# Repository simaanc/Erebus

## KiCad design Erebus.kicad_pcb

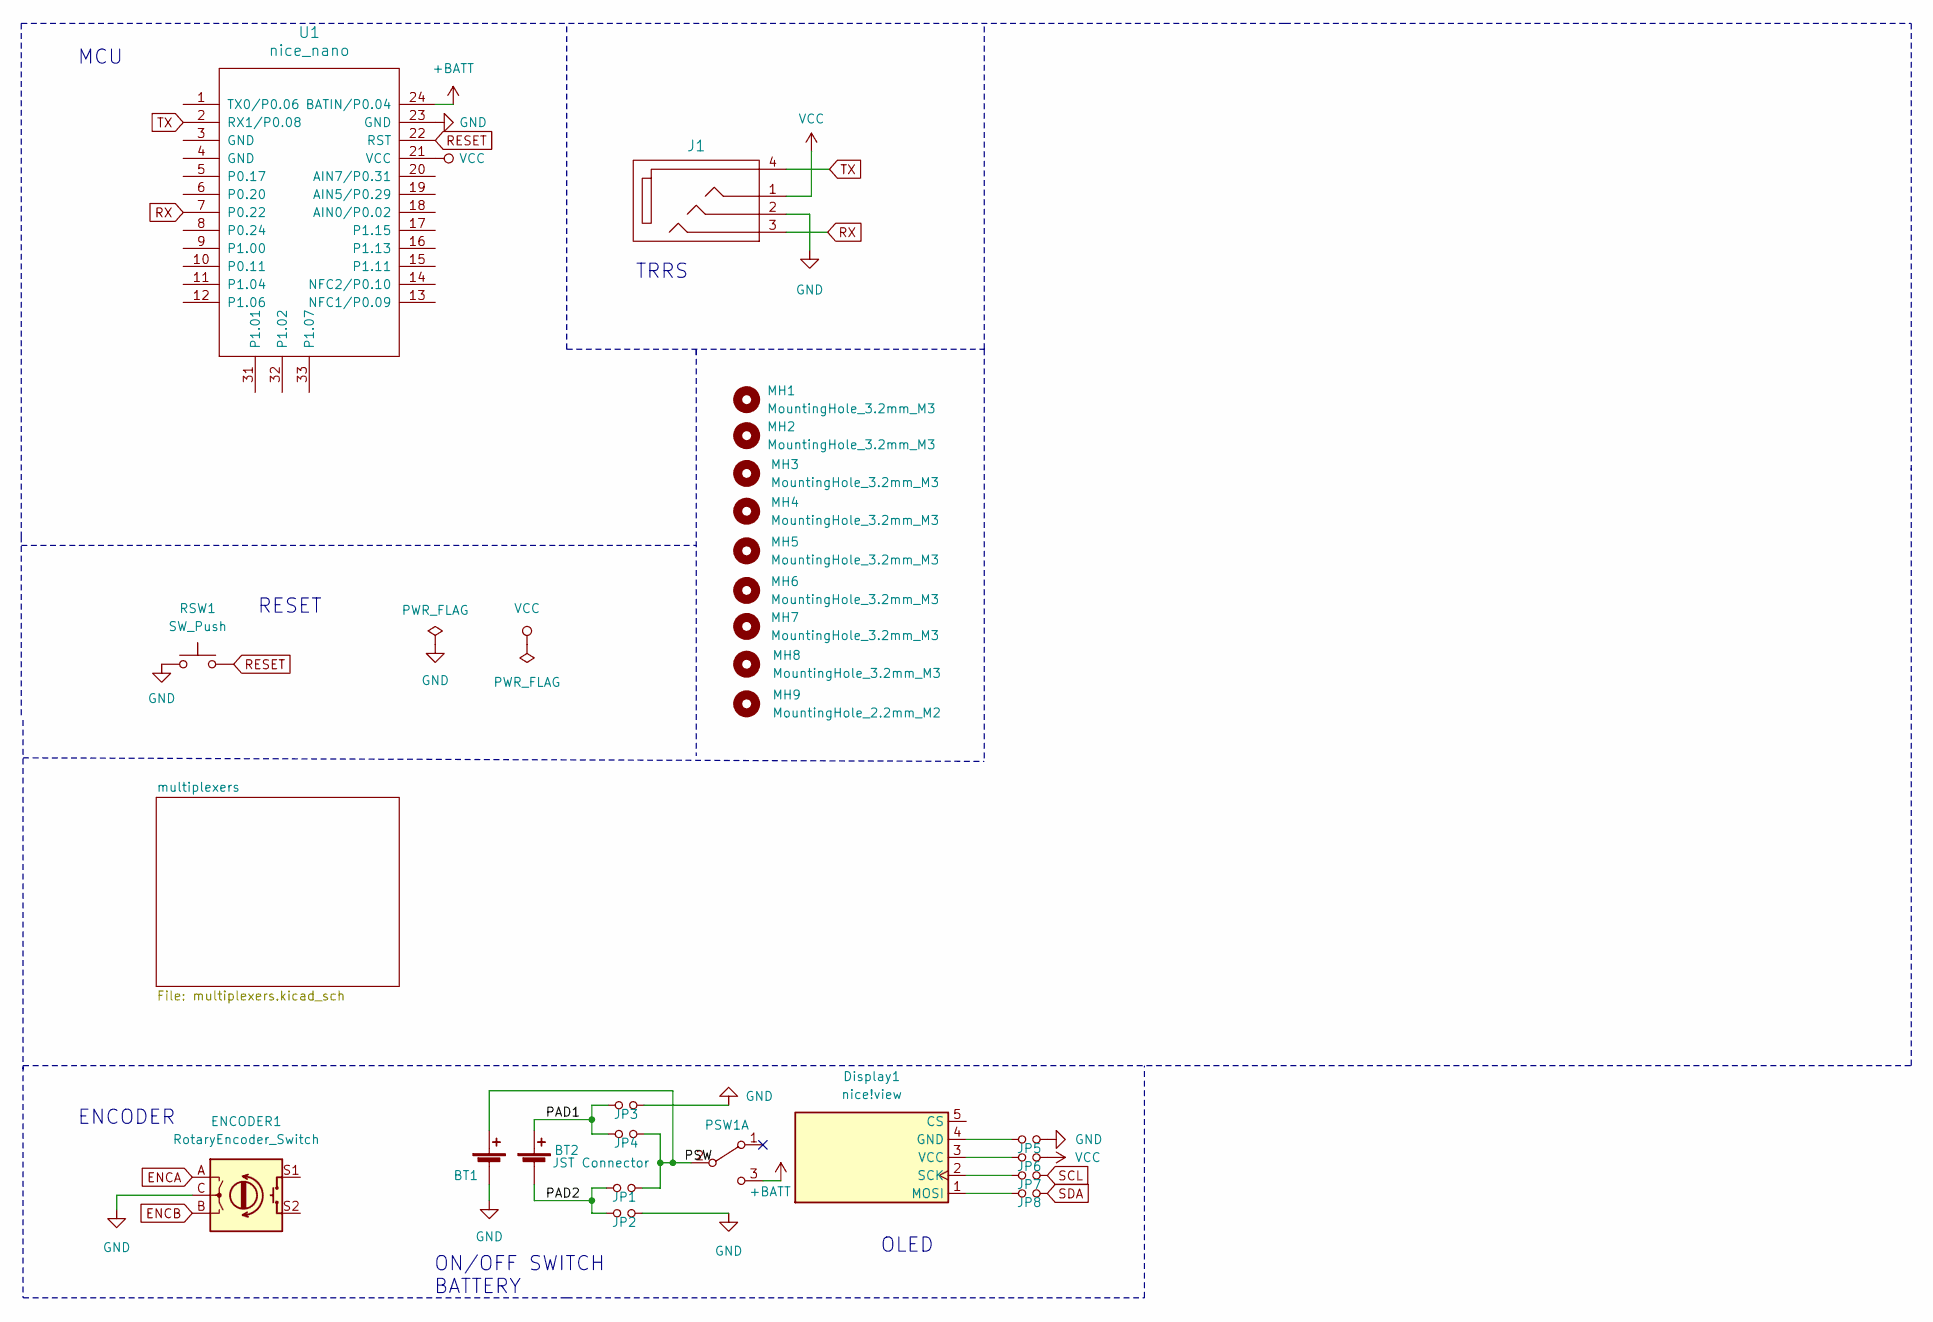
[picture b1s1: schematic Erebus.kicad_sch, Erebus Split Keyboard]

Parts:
BT1: Battery_Cell; custombatteryconnector_small
BT2: JST Connector; JST_PH_reversible
Display1: nice!view; nice_view
ENCODER1: RotaryEncoder_Switch; RotaryEncoder_Alps_EC11E-Switch_Vertical_H20mm-keebio_modif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
J1: MJ-4PP-9
JP1, JP2, JP3, JP4, JP5, JP6, JP7, JP8: Device_Jumper_NO_Small; Jumper
MH1, MH2, MH3, MH4, MH5, MH6, MH7, MH8: MountingHole_3.2mm_M3
MH9: MountingHole_2.2mm_M2
PSW1: SW_DPDT_x2; MSK12C02_reversible
RSW1: SW_Push; SW_Push_1P1T-MP_NO_Horizontal_Alps_SKRTLAE010_both_sides
U1: nice_nano

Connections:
+BATT: PSW1.3 (C), U1.24 (BATIN/P0.04)
/PAD1: BT2.1 (+), JP3.1, JP4.1
/PAD2: BT2.2 (-), JP1.1, JP2.1
/PSW: BT1.1 (+), JP1.2, JP4.2, PSW1.2 (B)
ENCA: ENCODER1.A
ENCB: ENCODER1.B
GND: BT1.2 (-), ENCODER1.C, J1.2, JP2.2, JP3.2, JP5.2, RSW1.1, U1.23 (GND); also elsewhere on the board
unnamed: Display1.4 (GND), JP5.1
unnamed: Display1.1 (MOSI), JP8.1
unnamed: Display1.2 (SCK), JP7.1
unnamed: Display1.3 (VCC), JP6.1
RESET: RSW1.2, U1.22 (RST)
RX: J1.3, U1.7 (P0.22)
SCL: JP7.2
SDA: JP8.2
TX: J1.4, U1.2 (RX1/P0.08)
VCC: J1.1, JP6.2, U1.21 (VCC)

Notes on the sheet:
MCU
ON/OFF SWITCH BATTERY
ENCODER
OLED
TRRS
RESET

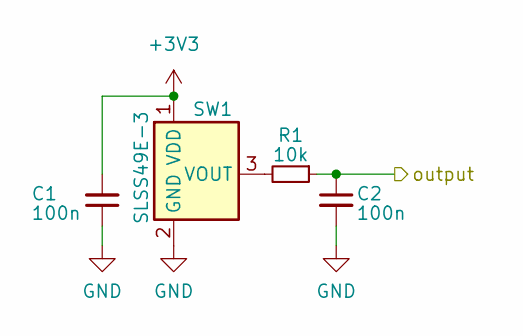
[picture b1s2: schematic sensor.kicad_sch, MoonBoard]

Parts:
C1, C2: 100n; C_0402_1005Metric
R1: 10k; R_0402_1005Metric
SW1: SLSS49E-3; SLSS49E-3 with MX holes

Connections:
+3V3: C1.2, SW1.1 (VDD); also elsewhere on the board
/multiplexers/keys/sensor0/output: C2.1, R1.1
GND: C1.1, C2.2, SW1.2 (GND); also elsewhere on the board
unnamed: R1.2, SW1.3 (VOUT)

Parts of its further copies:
C3, C4, C5, C6, C7, C8, C9, C10, C11, C12, C13, C14, C15, C16, C17, C18, C19, C20, C21, C22, C23, C24, C25, C26, C27, C28, C29, C30, C31, C32, C33, C34, C35, C36, C37, C38, C39, C40, C41, C42, C43, C44, C45, C46, C47, C48, C49, C50, C51, C52: 100n; C_0402_1005Metric
R2, R3, R4, R5, R6, R7, R8, R9, R10, R11, R12, R13, R14, R15, R16, R17, R18, R19, R20, R21, R22, R23, R24, R25, R26: 10k; R_0402_1005Metric
SW2, SW3, SW4, SW5, SW6, SW7, SW8, SW9, SW10, SW11, SW12, SW13, SW14, SW15, SW16, SW17, SW18, SW19, SW20, SW21, SW22, SW23, SW24, SW25, SW26: SLSS49E-3; SLSS49E-3 with MX holes

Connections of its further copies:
+3V3: C3.2, C5.2, C7.2, C9.2, C11.2, C13.2, C15.2, C17.2, C19.2, C21.2, C23.2, C25.2, C27.2, C29.2, C31.2, C33.2, C35.2, C37.2, C39.2, C41.2, C43.2, C45.2, C47.2, C49.2, C51.2, SW2.1 (VDD), SW3.1 (VDD), SW4.1 (VDD), SW5.1 (VDD), SW6.1 (VDD), SW7.1 (VDD), SW8.1 (VDD), SW9.1 (VDD), SW10.1 (VDD), SW11.1 (VDD), SW12.1 (VDD), SW13.1 (VDD), SW14.1 (VDD), SW15.1 (VDD), SW16.1 (VDD), SW17.1 (VDD), SW18.1 (VDD), SW19.1 (VDD), SW20.1 (VDD), SW21.1 (VDD), SW22.1 (VDD), SW23.1 (VDD), SW24.1 (VDD), SW25.1 (VDD), SW26.1 (VDD); also elsewhere on the board
/multiplexers/keys/sensor1/output: C4.1, R2.1
/multiplexers/keys/sensor2/output: C6.1, R3.1
/multiplexers/keys/sensor3/output: C8.1, R4.1
/multiplexers/keys/sensor4/output: C10.1, R5.1
/multiplexers/keys/sensor5/output: C12.1, R6.1
/multiplexers/keys/sensor6/output: C14.1, R7.1
/multiplexers/keys/sensor7/output: C16.1, R8.1
/multiplexers/keys/sensor8/output: C18.1, R9.1
/multiplexers/keys/sensor9/output: C20.1, R10.1
/multiplexers/keys/sensor10/output: C22.1, R11.1
/multiplexers/keys/sensor11/output: C24.1, R12.1
/multiplexers/keys/sensor12/output: C26.1, R13.1
/multiplexers/keys/sensor13/output: C28.1, R14.1
/multiplexers/keys/sensor14/output: C30.1, R15.1
/multiplexers/keys/sensor15/output: C32.1, R16.1
/multiplexers/keys/sensor16/output: C34.1, R17.1
/multiplexers/keys/sensor17/output: C36.1, R18.1
/multiplexers/keys/sensor18/output: C38.1, R19.1
/multiplexers/keys/sensor19/output: C40.1, R20.1
/multiplexers/keys/sensor20/output: C42.1, R21.1
/multiplexers/keys/sensor21/output: C44.1, R22.1
/multiplexers/keys/sensor23/output: C46.1, R23.1
/multiplexers/keys/sensor24/output: C48.1, R24.1
/multiplexers/keys/sensor25/output: C50.1, R25.1
/multiplexers/keys/sensor26/output: C52.1, R26.1
GND: C3.1, C4.2, C5.1, C6.2, C7.1, C8.2, C9.1, C10.2, C11.1, C12.2, C13.1, C14.2, C15.1, C16.2, C17.1, C18.2, C19.1, C20.2, C21.1, C22.2, C23.1, C24.2, C25.1, C26.2, C27.1, C28.2, C29.1, C30.2, C31.1, C32.2, C33.1, C34.2, C35.1, C36.2, C37.1, C38.2, C39.1, C40.2, C41.1, C42.2, C43.1, C44.2, C45.1, C46.2, C47.1, C48.2, C49.1, C50.2, C51.1, C52.2, SW2.2 (GND), SW3.2 (GND), SW4.2 (GND), SW5.2 (GND), SW6.2 (GND), SW7.2 (GND), SW8.2 (GND), SW9.2 (GND), SW10.2 (GND), SW11.2 (GND), SW12.2 (GND), SW13.2 (GND), SW14.2 (GND), SW15.2 (GND), SW16.2 (GND), SW17.2 (GND), SW18.2 (GND), SW19.2 (GND), SW20.2 (GND), SW21.2 (GND), SW22.2 (GND), SW23.2 (GND), SW24.2 (GND), SW25.2 (GND), SW26.2 (GND); also elsewhere on the board
unnamed: R2.2, SW2.3 (VOUT)
unnamed: R3.2, SW3.3 (VOUT)
unnamed: R4.2, SW4.3 (VOUT)
unnamed: R5.2, SW5.3 (VOUT)
unnamed: R6.2, SW6.3 (VOUT)
unnamed: R7.2, SW7.3 (VOUT)
unnamed: R8.2, SW8.3 (VOUT)
unnamed: R9.2, SW9.3 (VOUT)
unnamed: R10.2, SW10.3 (VOUT)
unnamed: R11.2, SW11.3 (VOUT)
unnamed: R12.2, SW12.3 (VOUT)
unnamed: R13.2, SW13.3 (VOUT)
unnamed: R14.2, SW14.3 (VOUT)
unnamed: R15.2, SW15.3 (VOUT)
unnamed: R16.2, SW16.3 (VOUT)
unnamed: R17.2, SW17.3 (VOUT)
unnamed: R18.2, SW18.3 (VOUT)
unnamed: R19.2, SW19.3 (VOUT)
unnamed: R20.2, SW20.3 (VOUT)
unnamed: R21.2, SW21.3 (VOUT)
unnamed: R22.2, SW22.3 (VOUT)
unnamed: R23.2, SW23.3 (VOUT)
unnamed: R24.2, SW24.3 (VOUT)
unnamed: R25.2, SW25.3 (VOUT)
unnamed: R26.2, SW26.3 (VOUT)

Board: 2 copper layers, 129 parts (0 on the bottom side), 66 nets, no tracks yet.

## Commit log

2024-02-18 Added Multiplexers and subpage
2024-02-20 Added All the Keyswitches Required
2024-02-27 Added Extra B and Started Multiplexer Layout
2024-02-27 Added All Keys to Multiplexers
2024-03-16 Setup Base Layout
2024-03-16 Migrating to AT32F415CBT7
2024-08-17 Routed a lot of the pcb, additionally fixed issues with wrong layout
2024-08-22 Finished routing all switches
2026-03-21 Switched to split layout ortholinear
2026-03-21 Fixed title block
2026-03-23 Added and finalized layout of switches
